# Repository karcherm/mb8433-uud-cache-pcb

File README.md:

1MB cache module for the Biostar MB-8433-UUD mainboard
======================================================

This adapter PCB enables you to install cache using SOJ32 chips, which are still in production. Furthermore,
with a modification of the mainboard, you can install up to 1MB of cache. To support 1MB of cache, you need
to grab A19 from the CPU and route it to the square header pin at the corner of this PCB.

Assembly hints
=========
For U1 to U8 (data RAM): Use 128k x 8 SRAM chips - the layout is not meant for 32k x 8 chips:
Neither does the address line ordering omit the "correct" lines if you install 32k x 8 chips,
nor is there sufficient bypassing at the Vcc pin for SOJ28 chips.

U9 can be a 128k x 8 or 64k x 8 SRAM chip. In case you just need 512K of cache, you can downgrade
U9 to 32k x 8. Sufficient bypassing for a 32k x 8 chip is present at this location. You can *not* downgrade
the data RAM to 64k x 8, though, as the address routing in version 1.1 is not adapted to this scenario.

Make sure to use sufficiently thin pins for plugging into the cache sockets.

Pay attention to the orientation of the memory chips: Pin 1 is always to the edge of the PCB, i.e.
U1-U4 are oriented the other way as U5-U9.

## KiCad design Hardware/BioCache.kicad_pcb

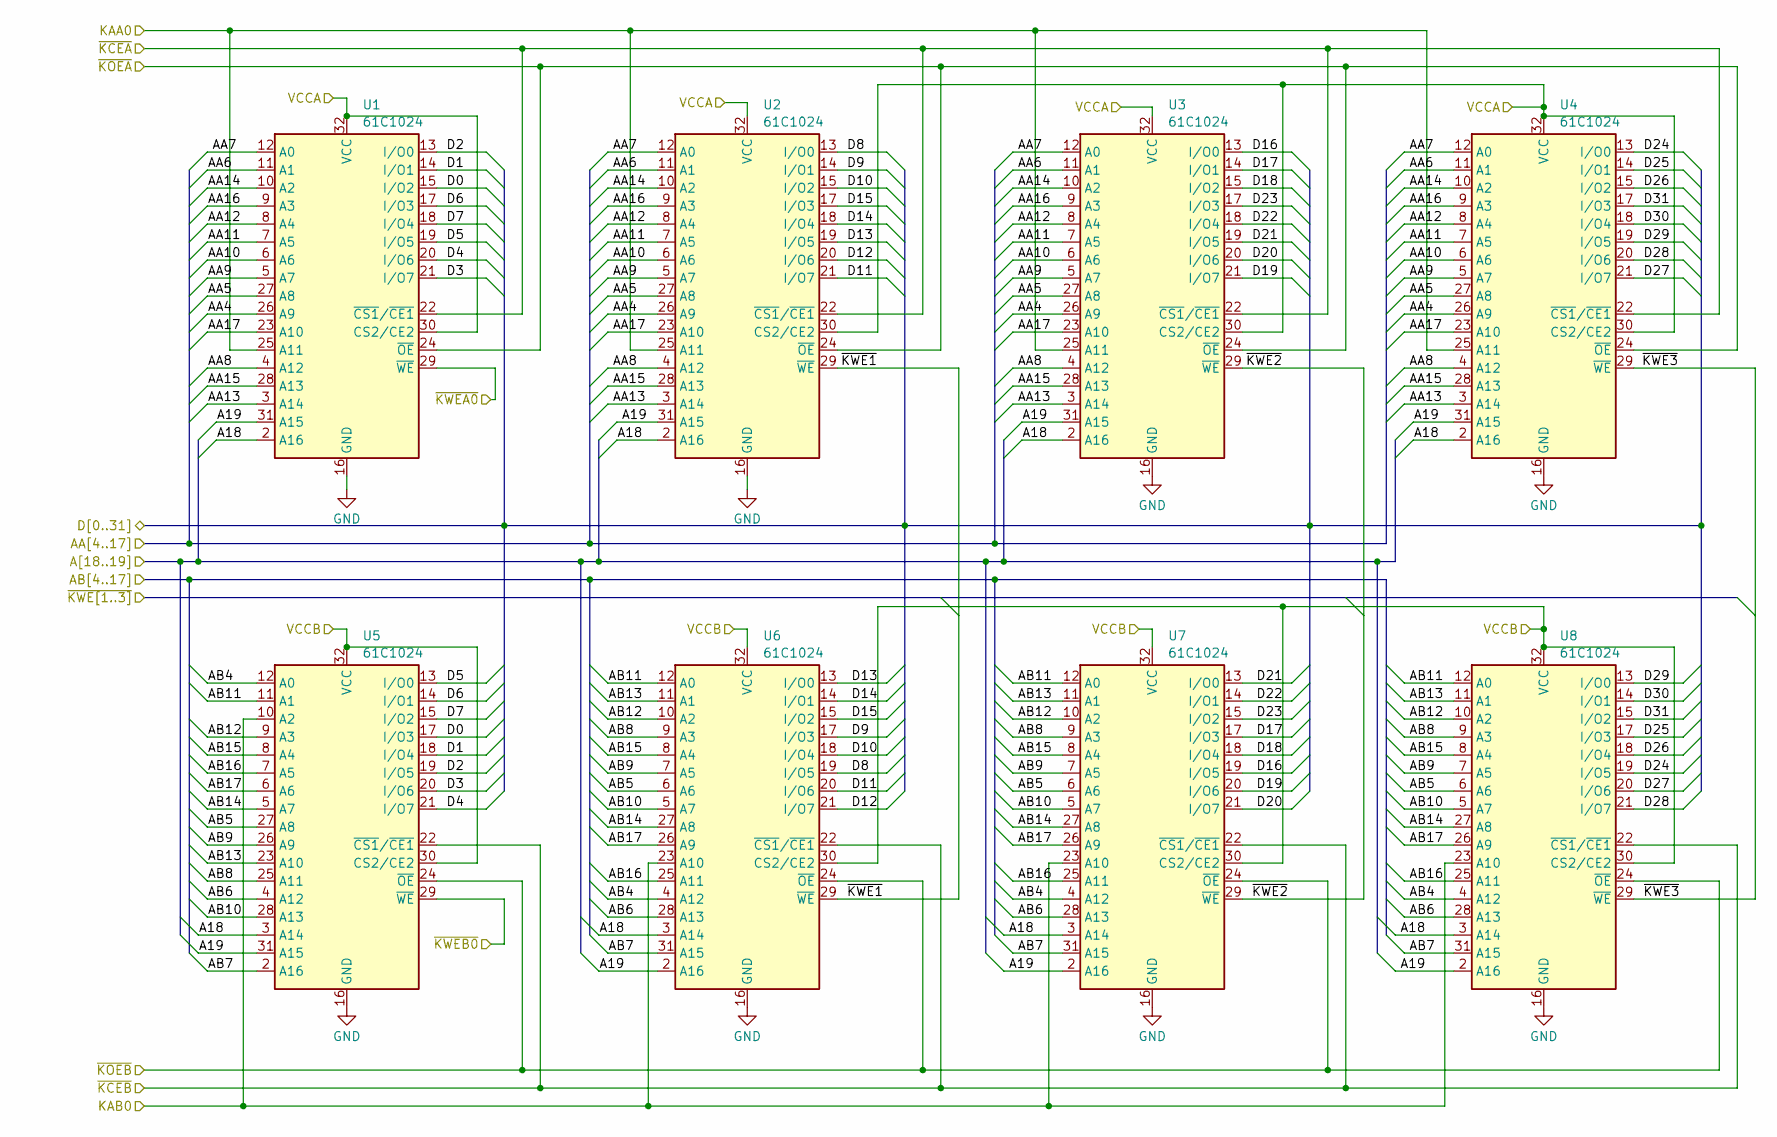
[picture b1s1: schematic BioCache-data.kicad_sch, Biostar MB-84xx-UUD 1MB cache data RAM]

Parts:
U1, U2, U3, U4, U5, U6, U7, U8: 61C1024; SOJ-32_7.62x20.955mm_P1.27mm

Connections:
/Data RAM/A18: U1.2 (A16), U2.2 (A16), U3.2 (A16), U4.2 (A16), U5.3 (A14), U6.3 (A14), U7.3 (A14), U8.3 (A14); also elsewhere on the board
/Data RAM/A19: U1.31 (A15), U2.31 (A15), U3.31 (A15), U4.31 (A15), U5.31 (A15), U6.2 (A16), U7.2 (A16), U8.2 (A16); also elsewhere on the board
/Data RAM/AA4: U1.26 (A9), U2.26 (A9), U3.26 (A9), U4.26 (A9); also elsewhere on the board
/Data RAM/AA5: U1.27 (A8), U2.27 (A8), U3.27 (A8), U4.27 (A8); also elsewhere on the board
/Data RAM/AA6: U1.11 (A1), U2.11 (A1), U3.11 (A1), U4.11 (A1); also elsewhere on the board
/Data RAM/AA7: U1.12 (A0), U2.12 (A0), U3.12 (A0), U4.12 (A0); also elsewhere on the board
/Data RAM/AA8: U1.4 (A12), U2.4 (A12), U3.4 (A12), U4.4 (A12); also elsewhere on the board
/Data RAM/AA9: U1.5 (A7), U2.5 (A7), U3.5 (A7), U4.5 (A7); also elsewhere on the board
/Data RAM/AA10: U1.6 (A6), U2.6 (A6), U3.6 (A6), U4.6 (A6); also elsewhere on the board
/Data RAM/AA11: U1.7 (A5), U2.7 (A5), U3.7 (A5), U4.7 (A5); also elsewhere on the board
/Data RAM/AA12: U1.8 (A4), U2.8 (A4), U3.8 (A4), U4.8 (A4); also elsewhere on the board
/Data RAM/AA13: U1.3 (A14), U2.3 (A14), U3.3 (A14), U4.3 (A14); also elsewhere on the board
/Data RAM/AA14: U1.10 (A2), U2.10 (A2), U3.10 (A2), U4.10 (A2); also elsewhere on the board
/Data RAM/AA15: U1.28 (A13), U2.28 (A13), U3.28 (A13), U4.28 (A13); also elsewhere on the board
/Data RAM/AA16: U1.9 (A3), U2.9 (A3), U3.9 (A3), U4.9 (A3); also elsewhere on the board
/Data RAM/AA17: U1.23 (A10), U2.23 (A10), U3.23 (A10), U4.23 (A10); also elsewhere on the board
/Data RAM/AB4: U5.12 (A0), U6.4 (A12), U7.4 (A12), U8.4 (A12); also elsewhere on the board
/Data RAM/AB5: U5.27 (A8), U6.6 (A6), U7.6 (A6), U8.6 (A6); also elsewhere on the board
/Data RAM/AB6: U5.4 (A12), U6.28 (A13), U7.28 (A13), U8.28 (A13); also elsewhere on the board
/Data RAM/AB7: U5.2 (A16), U6.31 (A15), U7.31 (A15), U8.31 (A15); also elsewhere on the board
/Data RAM/AB8: U5.25 (A11), U6.9 (A3), U7.9 (A3), U8.9 (A3); also elsewhere on the board
/Data RAM/AB9: U5.26 (A9), U6.7 (A5), U7.7 (A5), U8.7 (A5); also elsewhere on the board
/Data RAM/AB10: U5.28 (A13), U6.5 (A7), U7.5 (A7), U8.5 (A7); also elsewhere on the board
/Data RAM/AB11: U5.11 (A1), U6.12 (A0), U7.12 (A0), U8.12 (A0); also elsewhere on the board
/Data RAM/AB12: U5.9 (A3), U6.10 (A2), U7.10 (A2), U8.10 (A2); also elsewhere on the board
/Data RAM/AB13: U5.23 (A10), U6.11 (A1), U7.11 (A1), U8.11 (A1); also elsewhere on the board
/Data RAM/AB14: U5.5 (A7), U6.27 (A8), U7.27 (A8), U8.27 (A8); also elsewhere on the board
/Data RAM/AB15: U5.8 (A4), U6.8 (A4), U7.8 (A4), U8.8 (A4); also elsewhere on the board
/Data RAM/AB16: U5.7 (A5), U6.25 (A11), U7.25 (A11), U8.25 (A11); also elsewhere on the board
/Data RAM/AB17: U5.6 (A6), U6.26 (A9), U7.26 (A9), U8.26 (A9); also elsewhere on the board
/Data RAM/D0: U1.15 (I/O2), U5.17 (I/O3); also elsewhere on the board
/Data RAM/D1: U1.14 (I/O1), U5.18 (I/O4); also elsewhere on the board
/Data RAM/D2: U1.13 (I/O0), U5.19 (I/O5); also elsewhere on the board
/Data RAM/D3: U1.21 (I/O7), U5.20 (I/O6); also elsewhere on the board
/Data RAM/D4: U1.20 (I/O6), U5.21 (I/O7); also elsewhere on the board
/Data RAM/D5: U1.19 (I/O5), U5.13 (I/O0); also elsewhere on the board
/Data RAM/D6: U1.17 (I/O3), U5.14 (I/O1); also elsewhere on the board
/Data RAM/D7: U1.18 (I/O4), U5.15 (I/O2); also elsewhere on the board
/Data RAM/D8: U2.13 (I/O0), U6.19 (I/O5); also elsewhere on the board
/Data RAM/D9: U2.14 (I/O1), U6.17 (I/O3); also elsewhere on the board
/Data RAM/D10: U2.15 (I/O2), U6.18 (I/O4); also elsewhere on the board
/Data RAM/D11: U2.21 (I/O7), U6.20 (I/O6); also elsewhere on the board
/Data RAM/D12: U2.20 (I/O6), U6.21 (I/O7); also elsewhere on the board
/Data RAM/D13: U2.19 (I/O5), U6.13 (I/O0); also elsewhere on the board
/Data RAM/D14: U2.18 (I/O4), U6.14 (I/O1); also elsewhere on the board
/Data RAM/D15: U2.17 (I/O3), U6.15 (I/O2); also elsewhere on the board
/Data RAM/D16: U3.13 (I/O0), U7.19 (I/O5); also elsewhere on the board
/Data RAM/D17: U3.14 (I/O1), U7.17 (I/O3); also elsewhere on the board
/Data RAM/D18: U3.15 (I/O2), U7.18 (I/O4); also elsewhere on the board
/Data RAM/D19: U3.21 (I/O7), U7.20 (I/O6); also elsewhere on the board
/Data RAM/D20: U3.20 (I/O6), U7.21 (I/O7); also elsewhere on the board
/Data RAM/D21: U3.19 (I/O5), U7.13 (I/O0); also elsewhere on the board
/Data RAM/D22: U3.18 (I/O4), U7.14 (I/O1); also elsewhere on the board
/Data RAM/D23: U3.17 (I/O3), U7.15 (I/O2); also elsewhere on the board
/Data RAM/D24: U4.13 (I/O0), U8.19 (I/O5); also elsewhere on the board
/Data RAM/D25: U4.14 (I/O1), U8.17 (I/O3); also elsewhere on the board
/Data RAM/D26: U4.15 (I/O2), U8.18 (I/O4); also elsewhere on the board
/Data RAM/D27: U4.21 (I/O7), U8.20 (I/O6); also elsewhere on the board
/Data RAM/D28: U4.20 (I/O6), U8.21 (I/O7); also elsewhere on the board
/Data RAM/D29: U4.19 (I/O5), U8.13 (I/O0); also elsewhere on the board
/Data RAM/D30: U4.18 (I/O4), U8.14 (I/O1); also elsewhere on the board
/Data RAM/D31: U4.17 (I/O3), U8.15 (I/O2); also elsewhere on the board
/Data RAM/KAA0: U1.25 (A11), U2.25 (A11), U3.25 (A11), U4.25 (A11); also elsewhere on the board
/Data RAM/KAB0: U5.10 (A2), U6.23 (A10), U7.23 (A10), U8.23 (A10); also elsewhere on the board
/Data RAM/~KCEA: U1.22 (~CS1/~CE1), U2.22 (~CS1/~CE1), U3.22 (~CS1/~CE1), U4.22 (~CS1/~CE1); also elsewhere on the board
/Data RAM/~KCEB: U5.22 (~CS1/~CE1), U6.22 (~CS1/~CE1), U7.22 (~CS1/~CE1), U8.22 (~CS1/~CE1); also elsewhere on the board
/Data RAM/~KOEA: U1.24 (~OE), U2.24 (~OE), U3.24 (~OE), U4.24 (~OE); also elsewhere on the board
/Data RAM/~KOEB: U5.24 (~OE), U6.24 (~OE), U7.24 (~OE), U8.24 (~OE); also elsewhere on the board
/Data RAM/~KWE1: U2.29 (~WE), U6.29 (~WE); also elsewhere on the board
/Data RAM/~KWE2: U3.29 (~WE), U7.29 (~WE); also elsewhere on the board
/Data RAM/~KWE3: U4.29 (~WE), U8.29 (~WE); also elsewhere on the board
/Data RAM/~KWEA0: U1.29 (~WE); also elsewhere on the board
/Data RAM/~KWEB0: U5.29 (~WE); also elsewhere on the board
/Tag RAM and Connectors/VCCA: U1.30 (CS2/CE2), U1.32 (VCC), U2.30 (CS2/CE2), U2.32 (VCC), U3.30 (CS2/CE2), U3.32 (VCC), U4.30 (CS2/CE2), U4.32 (VCC); also elsewhere on the board
/Tag RAM and Connectors/VCCB: U5.30 (CS2/CE2), U5.32 (VCC), U6.30 (CS2/CE2), U6.32 (VCC), U7.30 (CS2/CE2), U7.32 (VCC), U8.30 (CS2/CE2), U8.32 (VCC); also elsewhere on the board
GND: U1.16 (GND), U2.16 (GND), U3.16 (GND), U4.16 (GND), U5.16 (GND), U6.16 (GND), U7.16 (GND), U8.16 (GND); also elsewhere on the board

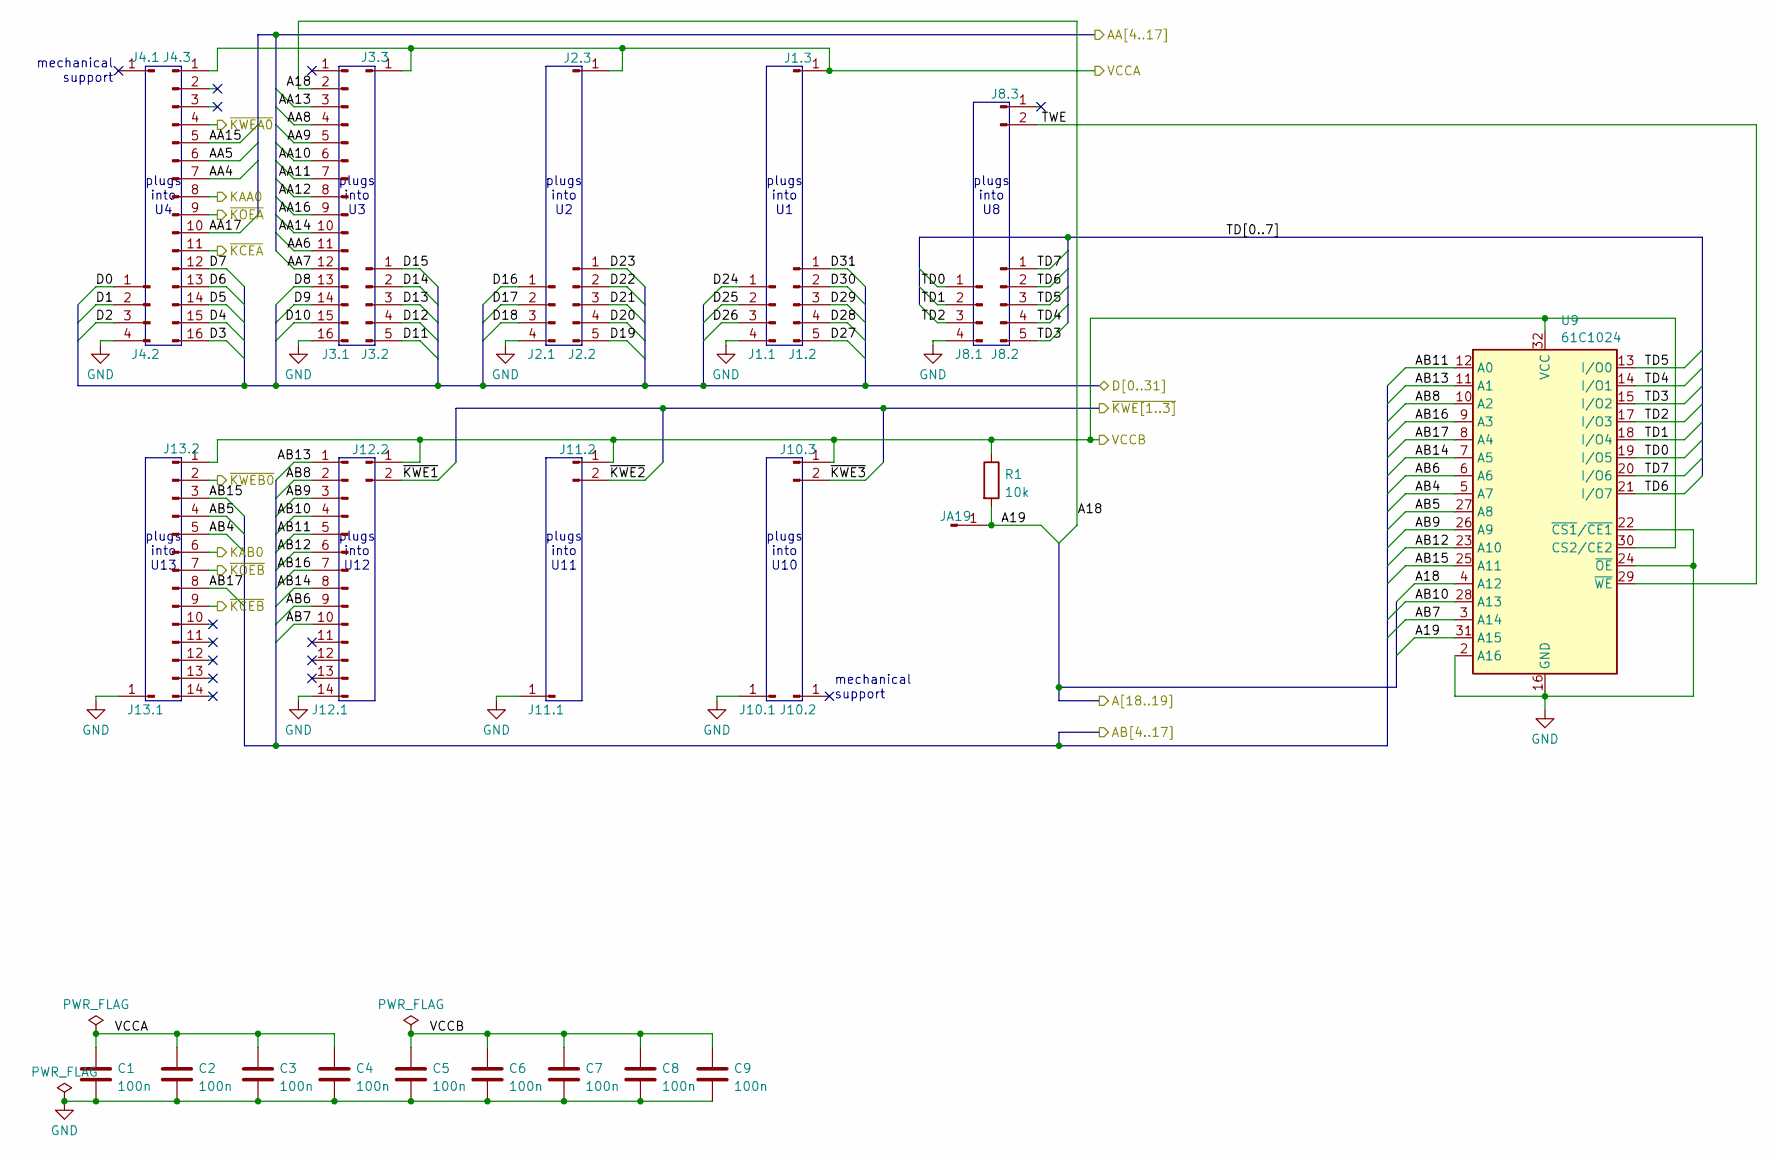
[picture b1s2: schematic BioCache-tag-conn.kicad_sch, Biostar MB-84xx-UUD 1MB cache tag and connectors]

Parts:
C1, C2, C3, C4, C5, C6, C7, C8, C9: 100n; C_0805_2012Metric_Pad1.18x1.45mm_HandSolder
J1.1, J2.1, J4.2, J8.1: Conn_01x04_Male; PinHeader_1x04_P2.54mm_Vertical_NoSquare1
J1.2, J2.2, J3.2, J8.2: Conn_01x05_Male; PinHeader_1x05_P2.54mm_Vertical_NoSquare1
J1.3, J2.3, J3.3, J4.1, J10.1, J10.2, J11.1, J13.1: Conn_01x01_Male; PinHeader_1x01_P2.54mm_Vertical_NoSquare1
J3.1, J4.3: Conn_01x16_Male; PinHeader_1x16_P2.54mm_Vertical_NoSquare1
J8.3, J10.3, J11.2, J12.2: Conn_01x02_Male; PinHeader_1x02_P2.54mm_Vertical_NoSquare1
J12.1, J13.2: Conn_01x14_Male; PinHeader_1x14_P2.54mm_Vertical_NoSquare1
JA19: Conn_01x01_Male; PinHeader_1x01_P2.54mm_Horizontal
R1: 10k; R_0805_2012Metric_Pad1.20x1.40mm_HandSolder
U9: 61C1024; SOJ-32_7.62x20.955mm_P1.27mm

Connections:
/Data RAM/A18: J3.1.2, U9.4 (A12); also elsewhere on the board
/Data RAM/A19: JA19.1, R1.2, U9.31 (A15); also elsewhere on the board
/Data RAM/AA4: J4.3.7; also elsewhere on the board
/Data RAM/AA5: J4.3.6; also elsewhere on the board
/Data RAM/AA6: J3.1.11; also elsewhere on the board
/Data RAM/AA7: J3.1.12; also elsewhere on the board
/Data RAM/AA8: J3.1.4; also elsewhere on the board
/Data RAM/AA9: J3.1.5; also elsewhere on the board
/Data RAM/AA10: J3.1.6; also elsewhere on the board
/Data RAM/AA11: J3.1.7; also elsewhere on the board
/Data RAM/AA12: J3.1.8; also elsewhere on the board
/Data RAM/AA13: J3.1.3; also elsewhere on the board
/Data RAM/AA14: J3.1.10; also elsewhere on the board
/Data RAM/AA15: J4.3.5; also elsewhere on the board
/Data RAM/AA16: J3.1.9; also elsewhere on the board
/Data RAM/AA17: J4.3.10; also elsewhere on the board
/Data RAM/AB4: J13.2.5, U9.5 (A7); also elsewhere on the board
/Data RAM/AB5: J13.2.4, U9.27 (A8); also elsewhere on the board
/Data RAM/AB6: J12.1.9, U9.6 (A6); also elsewhere on the board
/Data RAM/AB7: J12.1.10, U9.3 (A14); also elsewhere on the board
/Data RAM/AB8: J12.1.2, U9.10 (A2); also elsewhere on the board
/Data RAM/AB9: J12.1.3, U9.26 (A9); also elsewhere on the board
/Data RAM/AB10: J12.1.4, U9.28 (A13); also elsewhere on the board
/Data RAM/AB11: J12.1.5, U9.12 (A0); also elsewhere on the board
/Data RAM/AB12: J12.1.6, U9.23 (A10); also elsewhere on the board
/Data RAM/AB13: J12.1.1, U9.11 (A1); also elsewhere on the board
/Data RAM/AB14: J12.1.8, U9.7 (A5); also elsewhere on the board
/Data RAM/AB15: J13.2.3, U9.25 (A11); also elsewhere on the board
/Data RAM/AB16: J12.1.7, U9.9 (A3); also elsewhere on the board
/Data RAM/AB17: J13.2.8, U9.8 (A4); also elsewhere on the board
/Data RAM/D0: J4.2.1; also elsewhere on the board
/Data RAM/D1: J4.2.2; also elsewhere on the board
/Data RAM/D2: J4.2.3; also elsewhere on the board
/Data RAM/D3: J4.3.16; also elsewhere on the board
/Data RAM/D4: J4.3.15; also elsewhere on the board
/Data RAM/D5: J4.3.14; also elsewhere on the board
/Data RAM/D6: J4.3.13; also elsewhere on the board
/Data RAM/D7: J4.3.12; also elsewhere on the board
/Data RAM/D8: J3.1.13; also elsewhere on the board
/Data RAM/D9: J3.1.14; also elsewhere on the board
/Data RAM/D10: J3.1.15; also elsewhere on the board
/Data RAM/D11: J3.2.5; also elsewhere on the board
/Data RAM/D12: J3.2.4; also elsewhere on the board
/Data RAM/D13: J3.2.3; also elsewhere on the board
/Data RAM/D14: J3.2.2; also elsewhere on the board
/Data RAM/D15: J3.2.1; also elsewhere on the board
/Data RAM/D16: J2.1.1; also elsewhere on the board
/Data RAM/D17: J2.1.2; also elsewhere on the board
/Data RAM/D18: J2.1.3; also elsewhere on the board
/Data RAM/D19: J2.2.5; also elsewhere on the board
/Data RAM/D20: J2.2.4; also elsewhere on the board
/Data RAM/D21: J2.2.3; also elsewhere on the board
/Data RAM/D22: J2.2.2; also elsewhere on the board
/Data RAM/D23: J2.2.1; also elsewhere on the board
/Data RAM/D24: J1.1.1; also elsewhere on the board
/Data RAM/D25: J1.1.2; also elsewhere on the board
/Data RAM/D26: J1.1.3; also elsewhere on the board
/Data RAM/D27: J1.2.5; also elsewhere on the board
/Data RAM/D28: J1.2.4; also elsewhere on the board
/Data RAM/D29: J1.2.3; also elsewhere on the board
/Data RAM/D30: J1.2.2; also elsewhere on the board
/Data RAM/D31: J1.2.1; also elsewhere on the board
/Data RAM/KAA0: J4.3.8; also elsewhere on the board
/Data RAM/KAB0: J13.2.6; also elsewhere on the board
/Data RAM/~KCEA: J4.3.11; also elsewhere on the board
/Data RAM/~KCEB: J13.2.9; also elsewhere on the board
/Data RAM/~KOEA: J4.3.9; also elsewhere on the board
/Data RAM/~KOEB: J13.2.7; also elsewhere on the board
/Data RAM/~KWE1: J12.2.2; also elsewhere on the board
/Data RAM/~KWE2: J11.2.2; also elsewhere on the board
/Data RAM/~KWE3: J10.3.2; also elsewhere on the board
/Data RAM/~KWEA0: J4.3.4; also elsewhere on the board
/Data RAM/~KWEB0: J13.2.2; also elsewhere on the board
/Tag RAM and Connectors/TD0: J8.1.1, U9.19 (I/O5)
/Tag RAM and Connectors/TD1: J8.1.2, U9.18 (I/O4)
/Tag RAM and Connectors/TD2: J8.1.3, U9.17 (I/O3)
/Tag RAM and Connectors/TD3: J8.2.5, U9.15 (I/O2)
/Tag RAM and Connectors/TD4: J8.2.4, U9.14 (I/O1)
/Tag RAM and Connectors/TD5: J8.2.3, U9.13 (I/O0)
/Tag RAM and Connectors/TD6: J8.2.2, U9.21 (I/O7)
/Tag RAM and Connectors/TD7: J8.2.1, U9.20 (I/O6)
/Tag RAM and Connectors/TWE: J8.3.2, U9.29 (~WE)
/Tag RAM and Connectors/VCCA: C1.1, C2.1, C3.1, C4.1, J1.3.1, J2.3.1, J3.3.1, J4.3.1; also elsewhere on the board
/Tag RAM and Connectors/VCCB: C5.1, C6.1, C7.1, C8.1, C9.1, J10.3.1, J11.2.1, J12.2.1, J13.2.1, R1.1, U9.30 (CS2/CE2), U9.32 (VCC); also elsewhere on the board
GND: C1.2, C2.2, C3.2, C4.2, C5.2, C6.2, C7.2, C8.2, C9.2, J1.1.4, J2.1.4, J3.1.16, J4.2.4, J8.1.4, J10.1.1, J11.1.1, J12.1.14, J13.1.1, U9.2 (A16), U9.16 (GND), U9.22 (~CS1/~CE1), U9.24 (~OE); also elsewhere on the board

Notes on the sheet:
plugs into U11
plugs into U4
mechanical support
plugs into U12
plugs into U2
plugs into U10
plugs into U1
plugs into U8
plugs into U3
plugs into U13

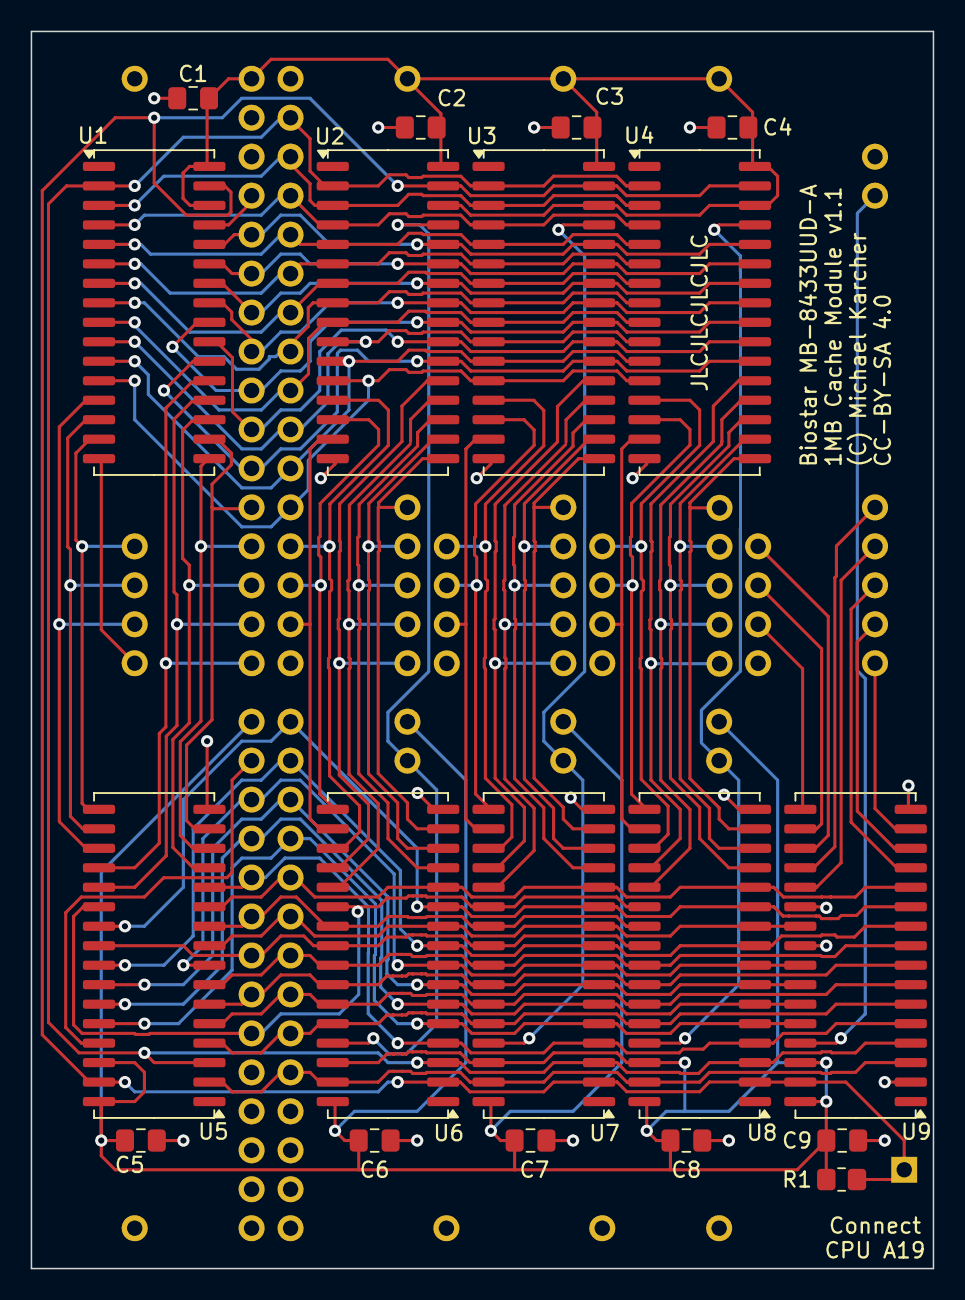
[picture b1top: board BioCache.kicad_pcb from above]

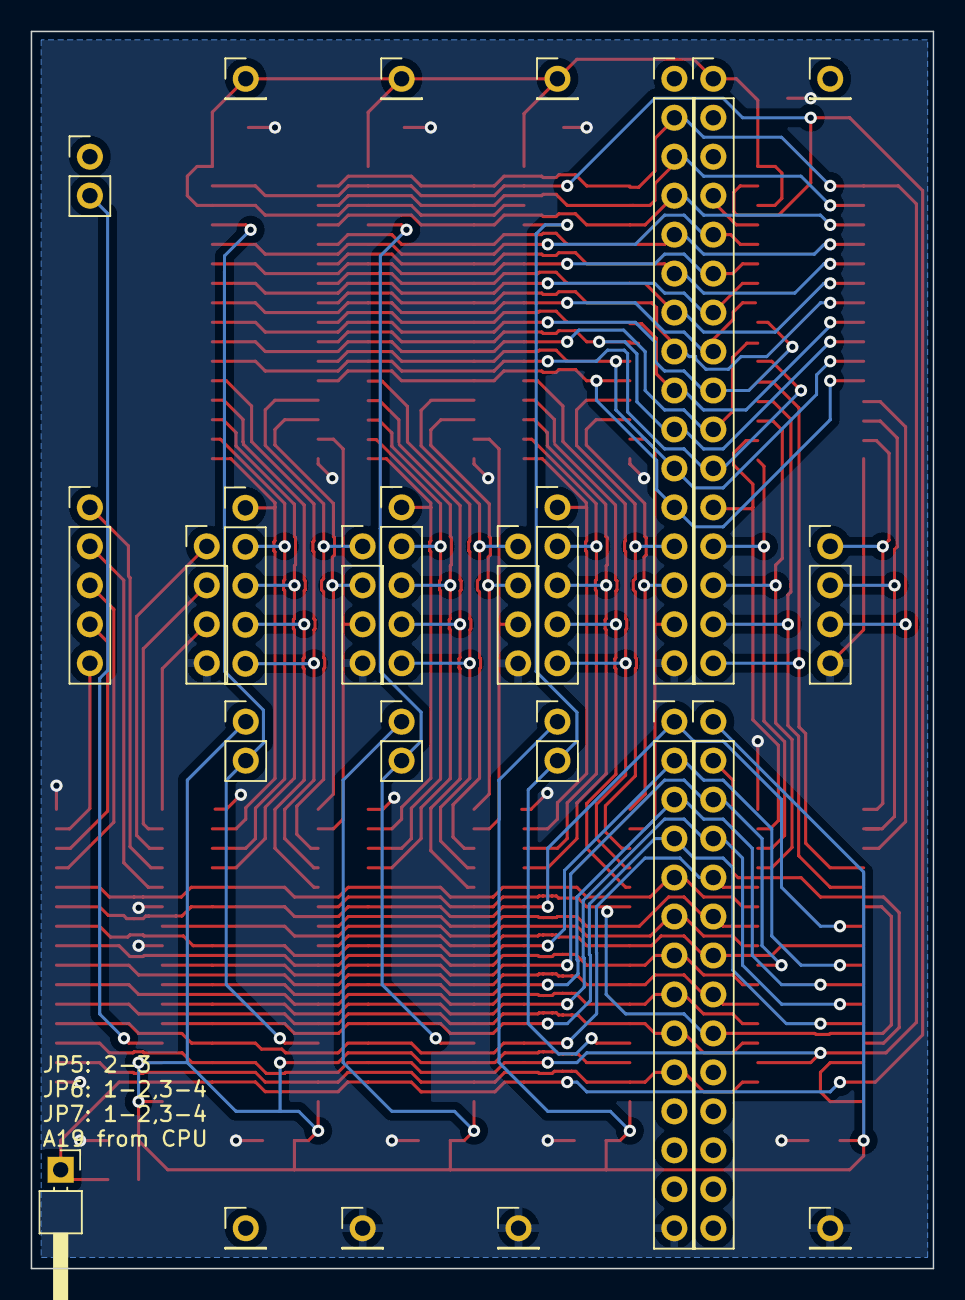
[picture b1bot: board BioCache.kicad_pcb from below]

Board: 2 copper layers, 58.8 x 80.6 mm, 44 parts (25 on the bottom side), 85 nets.

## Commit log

2023-08-05 Initial checkin of the hardware design
2023-08-05 SOJ library: Remove association with wrl files that don't exist
2023-08-05 Update PCB from library
2025-05-04 Upgrade to KiCad 9, clean-up schematics, set up KiBot
2025-05-04 add github workflow
2025-05-04 build KiCad stuff for releases
2025-05-04 Add LICENSE: CC-BY-SA-4.0
2025-05-09 Re-Route U9 (TAG ram) to support 32K*8 and 64K*8
2025-05-09 Ûpdate SOJ32 footprints to wider layout
    Reroute traces as required.
2025-05-09 Remove custom definition of SOJ32 memory chip
2025-05-09 Update modification date
2025-05-09 Add README.md
